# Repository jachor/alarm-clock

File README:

Method and apparatus for waking up.

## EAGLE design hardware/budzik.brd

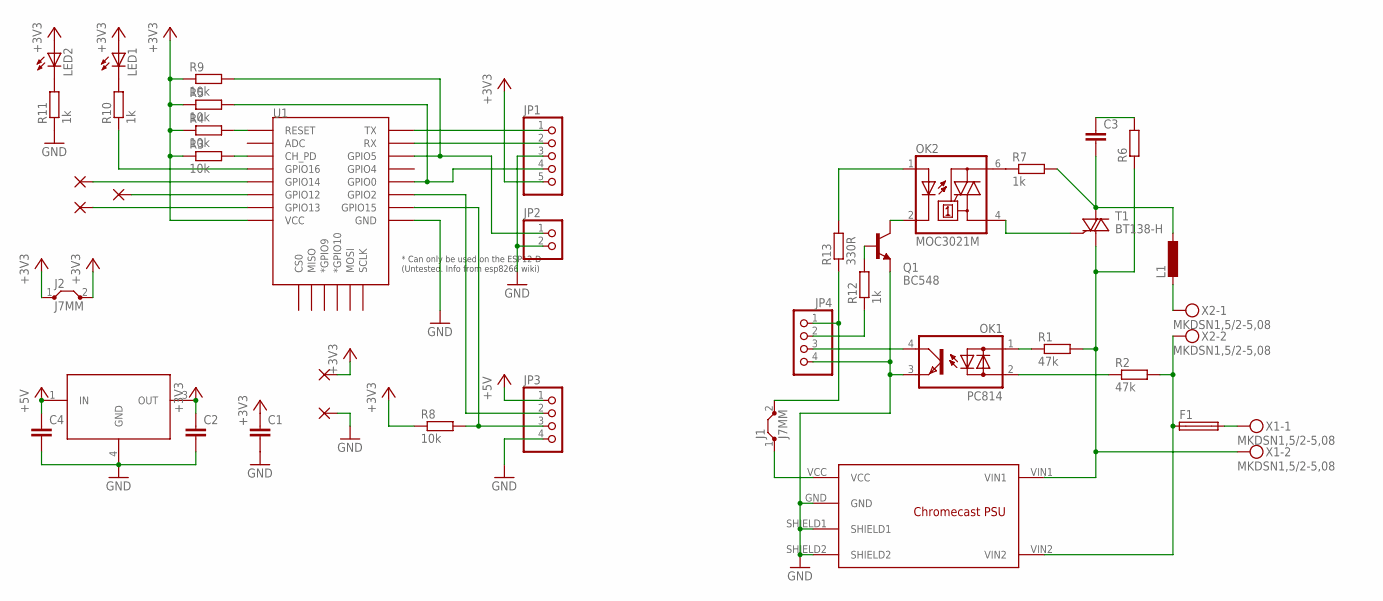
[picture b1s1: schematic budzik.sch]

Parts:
C1: C-EUC1206; C1206
C2, C4: C-EUC1206K; C1206K
C3: C-EU075-063X106; C075-063X106
F1: TR5
J1, J2: J7MM; 07
JP1: PINHD-1X5; 1X05
JP2: PINHD-1X2; 1X02
JP3, JP4: PINHD-1X4; 1X04
L1: L-EU6000-XXX-RC; 6000-XXXX-RC
LED1, LED2: LEDSML0805; SML0805
OK1: PC814; DIL04
OK2: MOC3021M; DIL06
PAD1, PAD2, PAD3, PAD4, PAD5: WIREPAD2,15/1,0; 2,15/1,0
Q1: BC548; TO92-EBC
R1, R2: 47k; 0204/7
R3, R4, R5, R8, R9: 10k; R0805
R6: R-EU_0411/3V; 0411V
R7: 1k; 0204/7
R10, R11, R12: 1k; R0805
R13: 330R; R0805
T1: BT138-H; TO220BH
U1: ESP12ESMD; ESP12E-SMD
U$1: CHROMECAST-PSU; CHROMECAST-PSU-UPSIDE-DOWN
U$2: LF33A; DPAK
X1, X2: MKDSN1,5/2-5,08

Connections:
+3V3: C1.1, C2.1, J2.1, J2.2, JP1.5, LED1.A, LED2.A, PAD4.1, R3.1, R4.1, R5.1, R8.1, R9.1, U1.VCC, U$2.3 (OUT)
+5V: C4.1, JP3.1, U$2.1 (IN)
GND: C1.2, C2.2, C4.2, JP1.3, JP2.2, JP3.4, JP4.4, OK1.3 (E), PAD5.1, Q1.E, R11.1, U1.GND, U$1.GND, U$1.SHIELD1, U$1.SHIELD2, U$2.4 (GND)
unnamed: C3.2, L1.1, R7.2, T1.T2 (A2)
unnamed: OK2.4 (A1), T1.G
unnamed: F1.2, X1.1
unnamed: R1.2, R6.1, T1.T1 (A1), U$1.VIN1, X1.2
unnamed: OK1.1 (AC1), R1.1
unnamed: OK1.2 (AC2), R2.1
unnamed: JP1.1, U1.TXD0 (TX)
unnamed: JP1.2, U1.RXD0 (RX)
unnamed: R3.2, U1.CH_PD
unnamed: JP1.4, R5.2, U1.GPIO0
unnamed: R4.2, U1.RESET
unnamed: F1.1, R2.2, U$1.VIN2, X2.2
unnamed: JP4.3, OK1.4 (C)
unnamed: JP3.3, R8.2, U1.GPIO15
unnamed: J1.2, JP4.1, R13.1
unnamed: C3.1, R6.2
unnamed: OK2.6 (A2), R7.1
unnamed: OK2.2 (C), Q1.C
unnamed: L1.2, X2.1
unnamed: OK2.1 (A), R13.2
unnamed: JP2.1, R9.2, U1.GPIO5
unnamed: PAD1.1, U1.GPIO13
unnamed: PAD2.1, U1.GPIO14
unnamed: PAD3.1, U1.GPIO12
unnamed: LED1.C, R10.2
unnamed: R10.1, U1.GPIO16
unnamed: LED2.C, R11.2
unnamed: JP4.2, R12.1
unnamed: Q1.B, R12.2
unnamed: JP3.2, U1.GPIO2
unnamed: J1.1, U$1.VCC

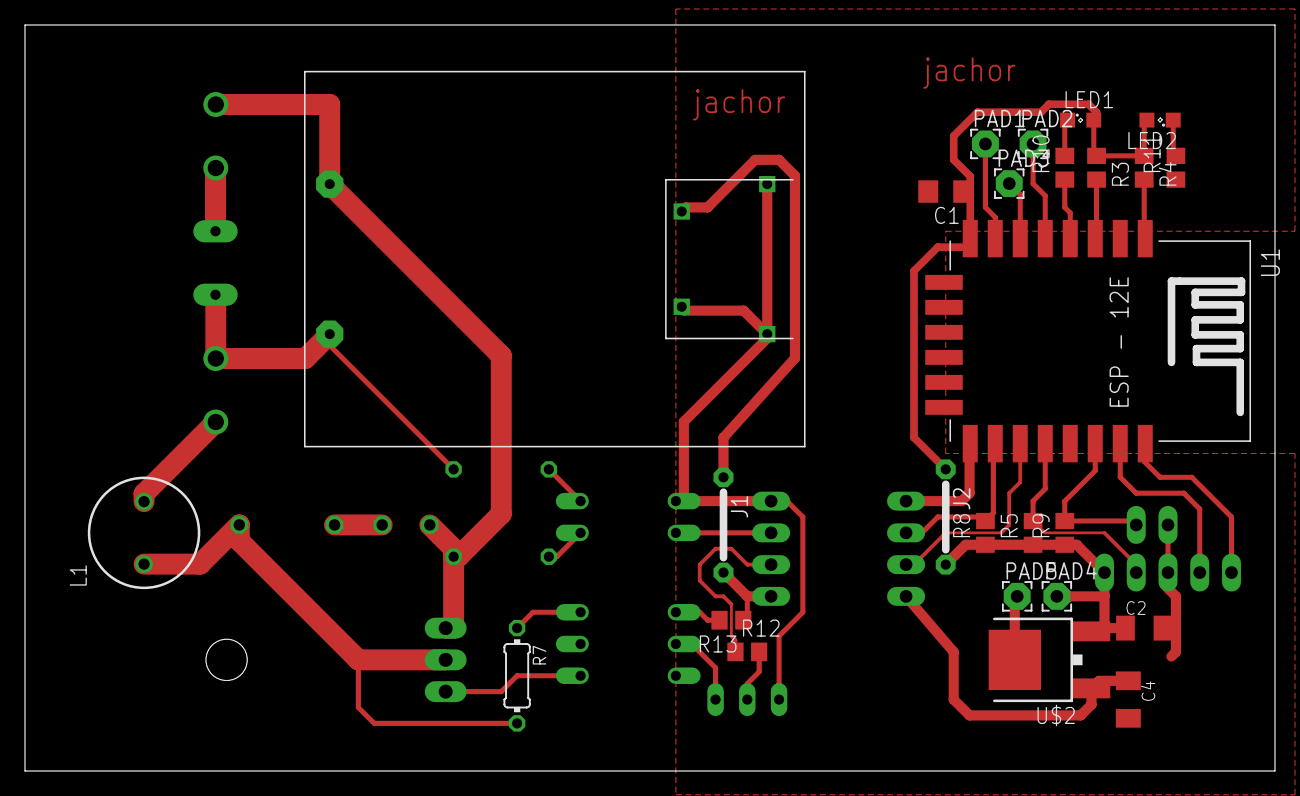
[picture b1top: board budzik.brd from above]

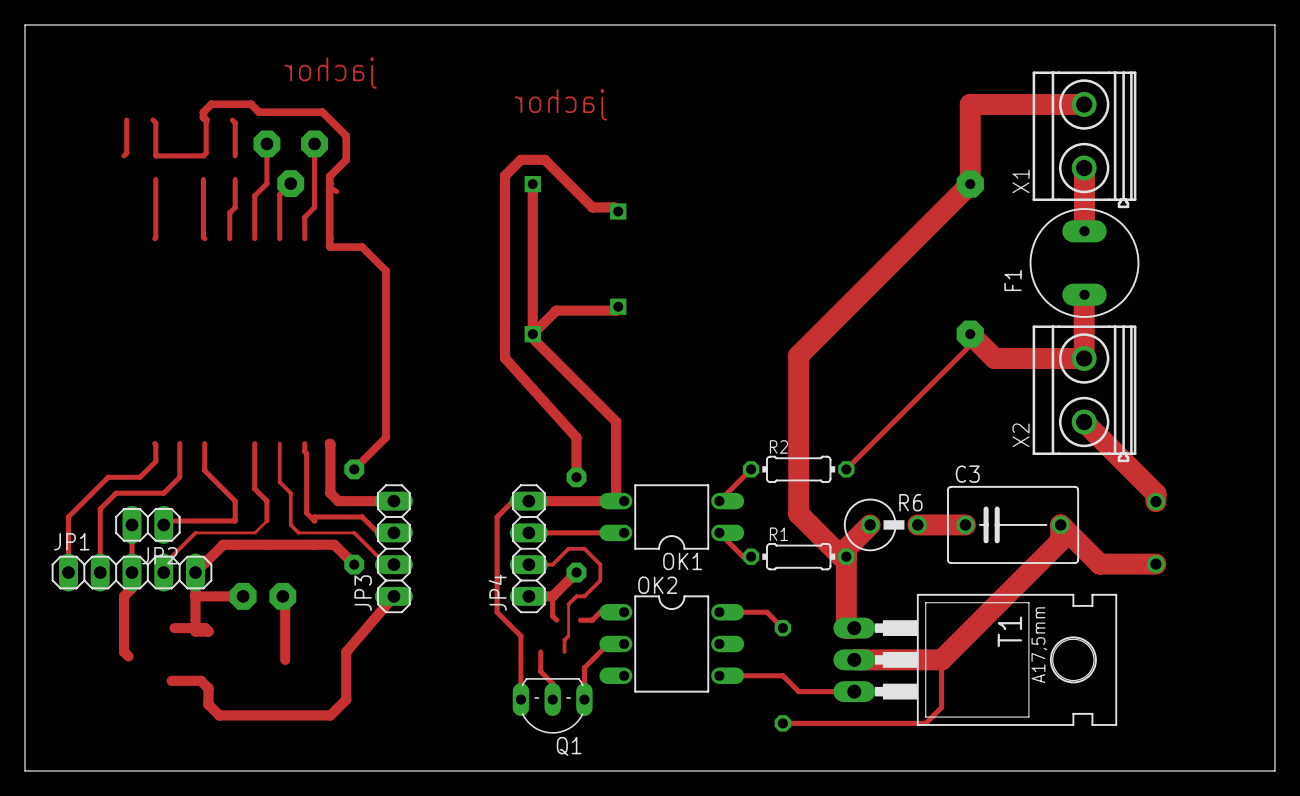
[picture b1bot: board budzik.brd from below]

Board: 2 copper layers, 100.0 x 59.7 mm, 41 parts (15 on the bottom side), 34 nets.

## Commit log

2018-01-26 esp8266 firmware
2018-01-26 schematics
2018-01-26 Android app
2018-01-27 docs index page
2018-01-27 Set theme jekyll-theme-architect
